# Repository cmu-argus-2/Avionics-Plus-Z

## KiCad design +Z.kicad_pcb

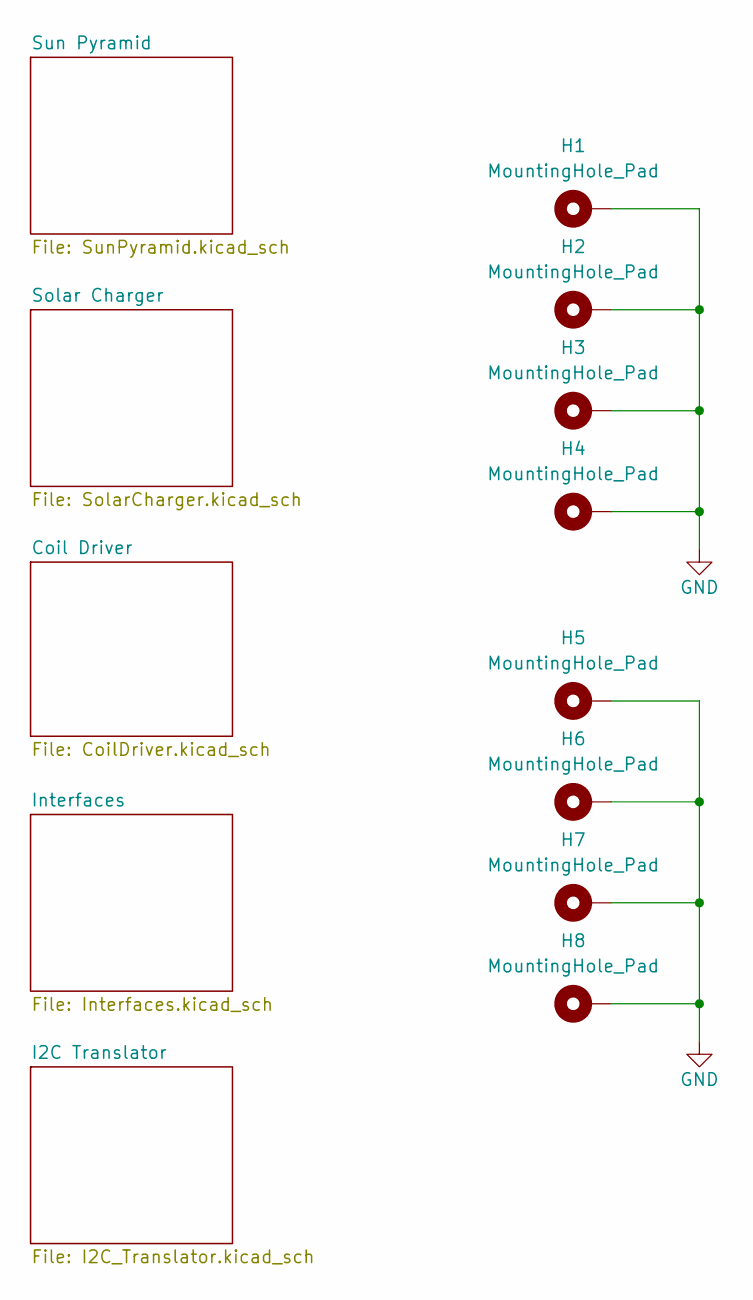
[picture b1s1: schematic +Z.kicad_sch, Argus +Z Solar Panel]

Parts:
H1, H2, H3, H4, H5, H6, H7, H8: MountingHole_Pad; MountingHole_3.2mm_M3_DIN965_Pad_TopBottom

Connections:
GND: H1.1, H2.1, H3.1, H4.1, H5.1, H6.1, H7.1, H8.1; also elsewhere on the board

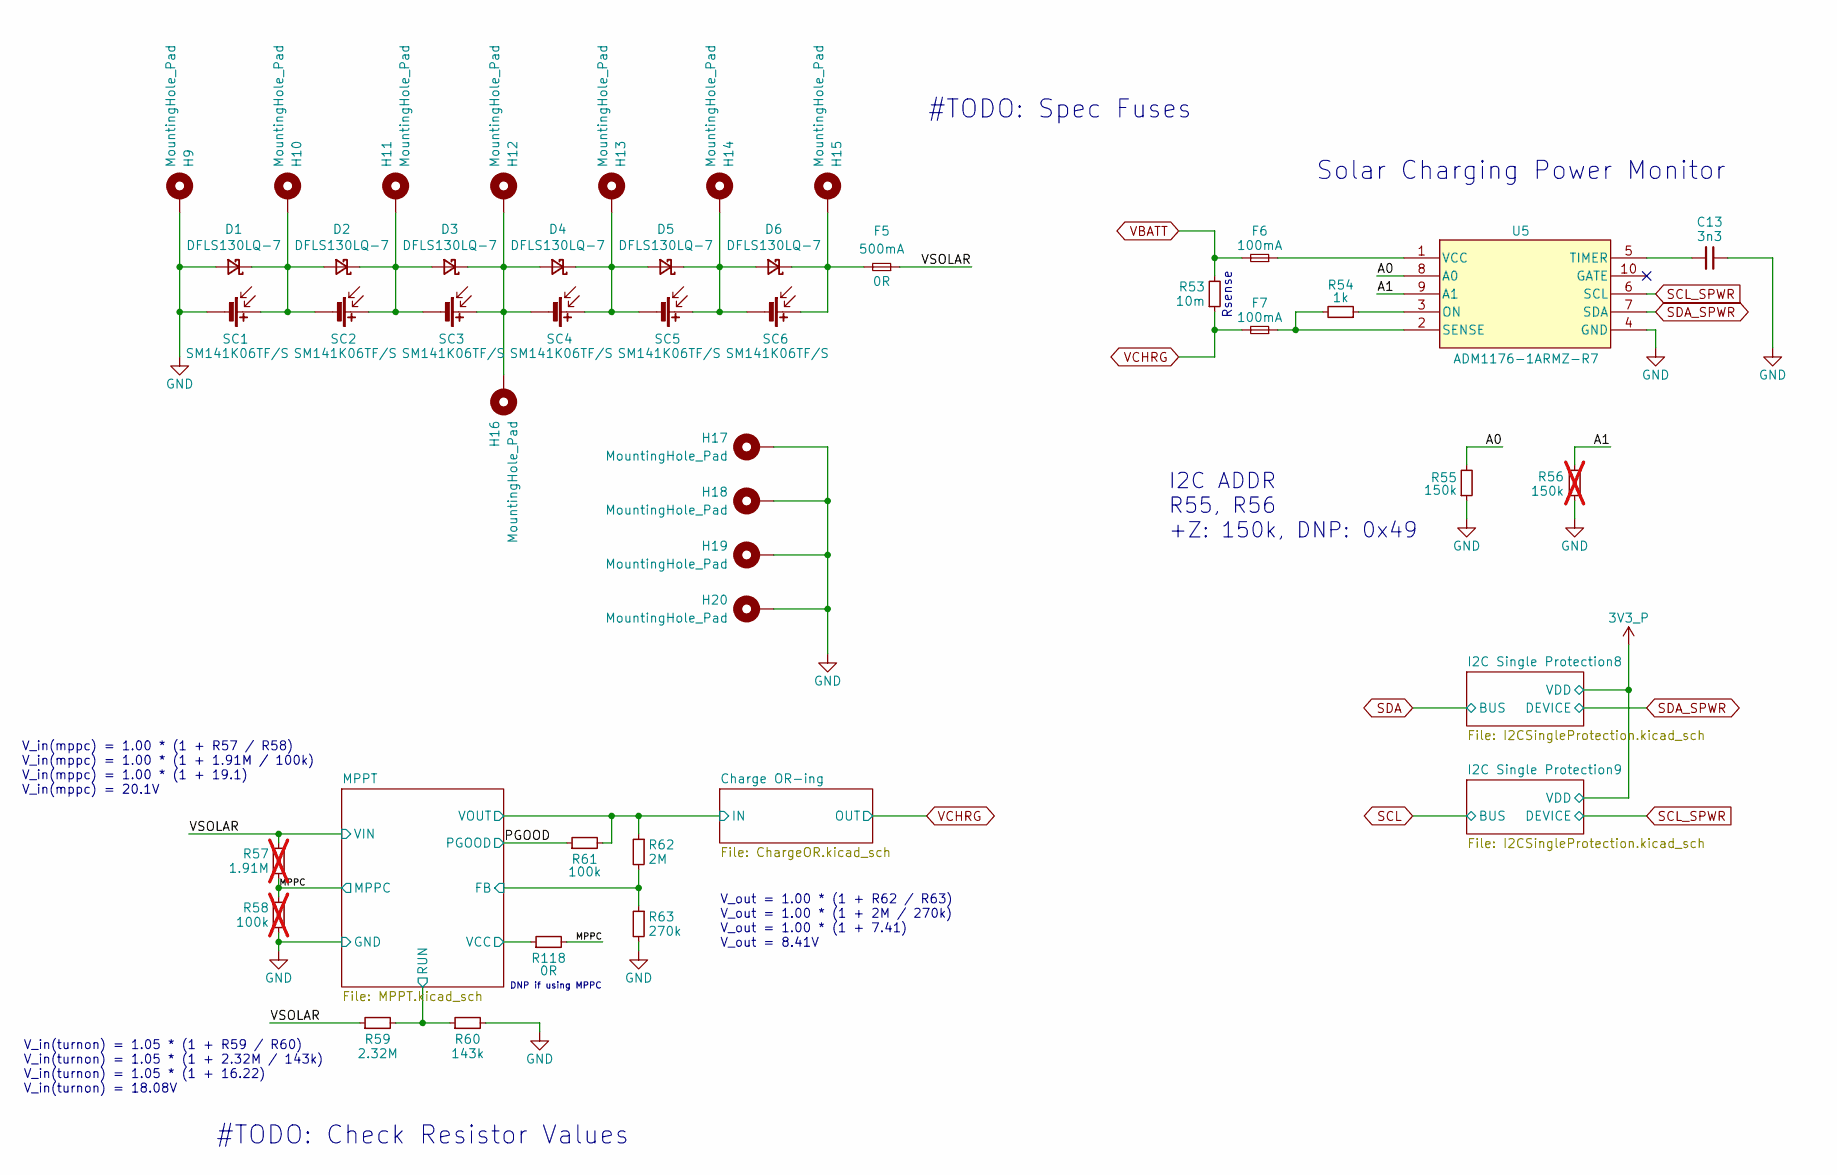
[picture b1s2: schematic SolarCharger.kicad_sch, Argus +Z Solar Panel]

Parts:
C13: 3n3; C_0603_1608Metric; MPN C3877267
D1, D2, D3, D4, D5, D6: DFLS130LQ-7; D_PowerDI-123
F5: 500mA; Fuse_0603_1608Metric
F6, F7: 100mA; Fuse_0603_1608Metric
H9, H10, H11, H12, H13, H14, H15, H16, H17, H18, H19, H20: MountingHole_Pad; TestPoint_Pad_D1.0mm
R53: 10m; R_2512_6332Metric; MPN C840621
R54: 1k; R_0603_1608Metric; MPN C2484712
R55: 150k; R_0603_1608Metric
R56: 150k; R_0603_1608Metric; MPN C402995; not fitted
R57: 1.91M; R_0603_1608Metric; not fitted
R58: 100k; R_0603_1608Metric; not fitted
R59: 2.32M; R_0603_1608Metric
R60: 143k; R_0603_1608Metric
R61: 100k; R_0603_1608Metric; MPN C237792
R62: 2M; R_0603_1608Metric
R63: 270k; R_0603_1608Metric; MPN C118142
R118: 0R; R_0603_1608Metric; MPN C237792
SC1, SC2, SC3, SC4, SC5, SC6: SM141K06TF/S; SM141K06TF_S
U5: ADM1176-1ARMZ-R7; MSOP-10_3x3mm_P0.5mm; Manufacturer_Part_Number ADM1176-1ARMZ-R7

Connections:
/Solar Charger/A0: R55.2, U5.8 (A0)
/Solar Charger/A1: R56.2, U5.9 (A1)
/Solar Charger/Charge OR-ing/IN: R61.2, R62.1; also elsewhere on the board
/Solar Charger/MPPC: R57.2, R58.1, R118.2; also elsewhere on the board
/Solar Charger/MPPT/FB: R62.2, R63.1; also elsewhere on the board
/Solar Charger/MPPT/RUN: R59.2, R60.1; also elsewhere on the board
/Solar Charger/MPPT/VCC: R118.1; also elsewhere on the board
/Solar Charger/PGOOD: R61.1; also elsewhere on the board
/Solar Charger/VSOLAR: F5.1, R57.1, R59.1; also elsewhere on the board
GND: C13.1, D1.2 (A), H9.1, H17.1, H18.1, H19.1, H20.1, R55.1, R56.1, R58.2, R60.2, R63.2, SC1.2 (-), U5.4 (GND); also elsewhere on the board
unnamed: D1.1 (K), D2.2 (A), H10.1, SC1.1 (+), SC2.2 (-)
unnamed: D2.1 (K), D3.2 (A), H11.1, SC2.1 (+), SC3.2 (-)
unnamed: D3.1 (K), D4.2 (A), H12.1, H16.1, SC3.1 (+), SC4.2 (-)
unnamed: D4.1 (K), D5.2 (A), H13.1, SC4.1 (+), SC5.2 (-)
unnamed: D5.1 (K), D6.2 (A), H14.1, SC5.1 (+), SC6.2 (-)
unnamed: D6.1 (K), F5.2, H15.1, SC6.1 (+)
unnamed: R54.1, U5.3 (ON)
unnamed: F7.1, R54.2, U5.2 (SENSE)
unnamed: C13.2, U5.5 (TIMER)
unnamed: F6.1, U5.1 (VCC)
SCL_SPWR: U5.6 (SCL); also elsewhere on the board
SDA_SPWR: U5.7 (SDA); also elsewhere on the board
VBATT: F6.2, R53.2; also elsewhere on the board
VCHRG: F7.2, R53.1; also elsewhere on the board

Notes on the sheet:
V_in(mppc) = 1.00 * (1 + R57 / R58) V_in(mppc) = 1.00 * (1 + 1.91M / 100k) V_in(mppc) = 1.00 * (1 + 19.1) V_in(mppc) = 20.1V
#TODO: Spec Fuses
V_in(turnon) = 1.05 * (1 + R59 / R60) V_in(turnon) = 1.05 * (1 + 2.32M / 143k) V_in(turnon) = 1.05 * (1 + 16.22) V_in(turnon) = 18.08V
Rsense
V_out = 1.00 * (1 + R62 / R63) V_out = 1.00 * (1 + 2M / 270k) V_out = 1.00 * (1 + 7.41) V_out = 8.41V
#TODO: Check Resistor Values
DNP if using MPPC
I2C ADDR R55, R56 +Z: 150k, DNP: 0x49
Solar Charging Power Monitor

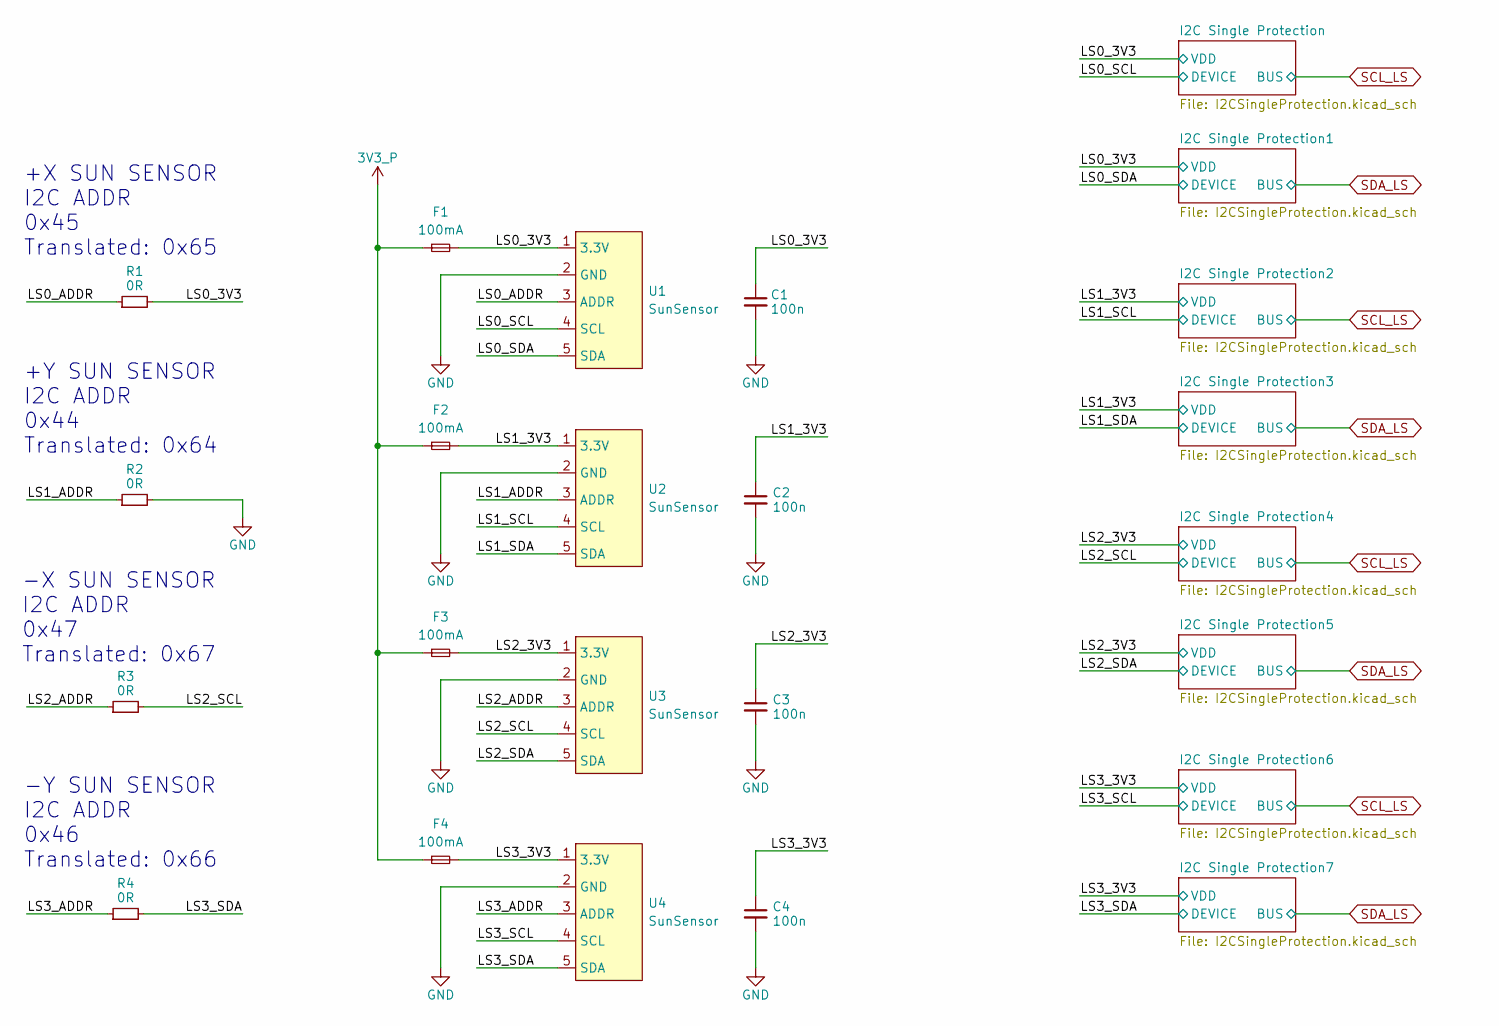
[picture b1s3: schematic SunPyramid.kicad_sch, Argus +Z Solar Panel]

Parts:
C1, C2, C3, C4: 100n; C_0603_1608Metric; MPN C307348
F1, F2, F3, F4: 100mA; Fuse_0603_1608Metric
R1, R2, R3, R4: 0R; R_0603_1608Metric; MPN C844915
U1, U2, U3, U4: SunSensor

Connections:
3V3_P: F1.1, F2.1, F3.1, F4.1; also elsewhere on the board
/Sun Pyramid/LS0_3V3: C1.1, F1.2, R1.2, U1.1 (3.3V); also elsewhere on the board
/Sun Pyramid/LS0_ADDR: R1.1, U1.3 (ADDR)
/Sun Pyramid/LS0_SCL: U1.4 (SCL); also elsewhere on the board
/Sun Pyramid/LS0_SDA: U1.5 (SDA); also elsewhere on the board
/Sun Pyramid/LS1_3V3: C2.1, F2.2, U2.1 (3.3V); also elsewhere on the board
/Sun Pyramid/LS1_ADDR: R2.1, U2.3 (ADDR)
/Sun Pyramid/LS1_SCL: U2.4 (SCL); also elsewhere on the board
/Sun Pyramid/LS1_SDA: U2.5 (SDA); also elsewhere on the board
/Sun Pyramid/LS2_3V3: C3.1, F3.2, U3.1 (3.3V); also elsewhere on the board
/Sun Pyramid/LS2_ADDR: R3.1, U3.3 (ADDR)
/Sun Pyramid/LS2_SCL: R3.2, U3.4 (SCL); also elsewhere on the board
/Sun Pyramid/LS2_SDA: U3.5 (SDA); also elsewhere on the board
/Sun Pyramid/LS3_3V3: C4.1, F4.2, U4.1 (3.3V); also elsewhere on the board
/Sun Pyramid/LS3_ADDR: R4.1, U4.3 (ADDR)
/Sun Pyramid/LS3_SCL: U4.4 (SCL); also elsewhere on the board
/Sun Pyramid/LS3_SDA: R4.2, U4.5 (SDA); also elsewhere on the board
GND: C1.2, C2.2, C3.2, C4.2, R2.2, U1.2 (GND), U2.2 (GND), U3.2 (GND), U4.2 (GND); also elsewhere on the board

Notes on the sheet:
-Y SUN SENSOR I2C ADDR 0x46 Translated: 0x66
-X SUN SENSOR I2C ADDR 0x47 Translated: 0x67
+X SUN SENSOR I2C ADDR 0x45 Translated: 0x65
+Y SUN SENSOR I2C ADDR 0x44 Translated: 0x64

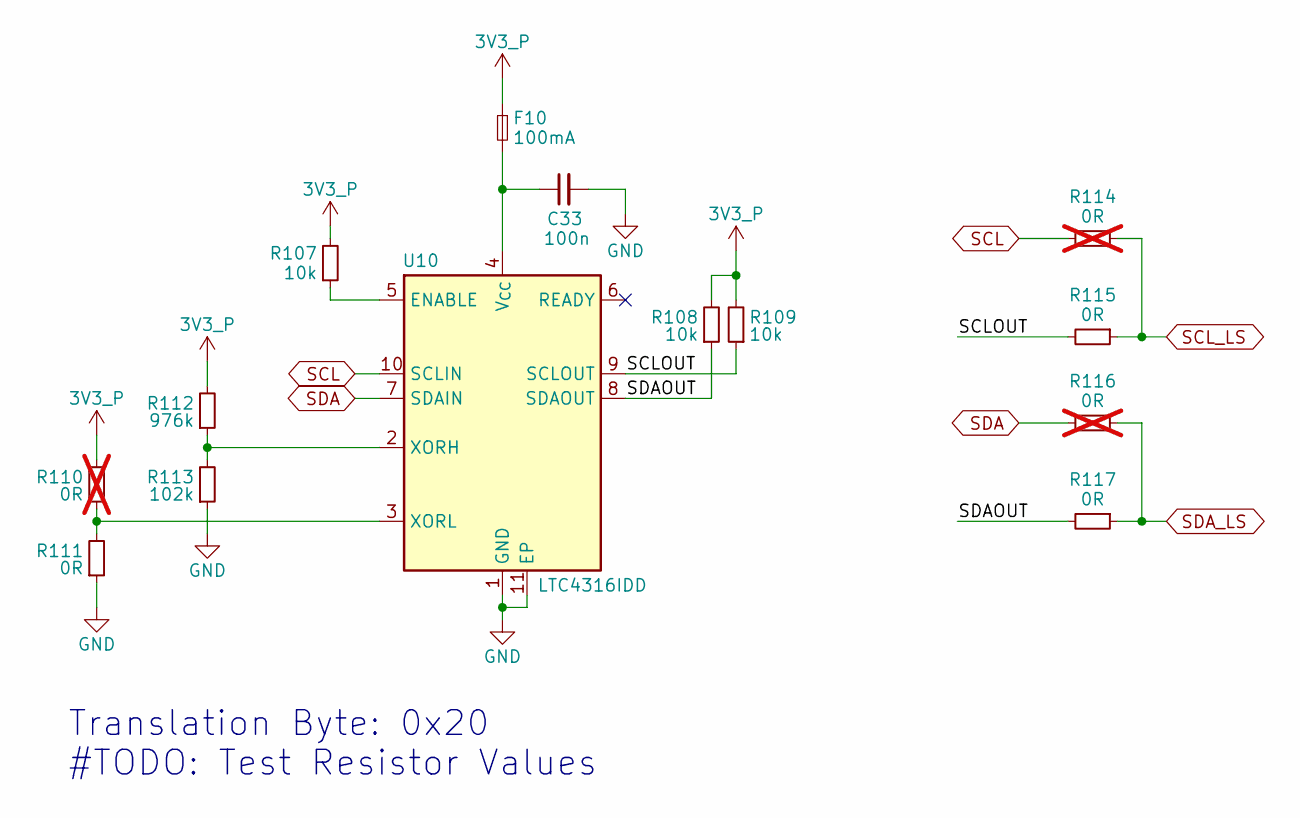
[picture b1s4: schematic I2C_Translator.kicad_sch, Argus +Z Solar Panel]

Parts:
C33: 100n; C_0603_1608Metric; MPN C307348
F10: 100mA; Fuse_0603_1608Metric
R107, R108, R109: 10k; R_0603_1608Metric; MPN C2479067
R110, R114, R116: 0R; R_0603_1608Metric; not fitted
R111, R115, R117: 0R; R_0603_1608Metric; MPN C844915
R112: 976k; R_0603_1608Metric
R113: 102k; R_0603_1608Metric
U10: LTC4316IDD; DFN-10-1EP_3x3mm_P0.5mm_EP1.65x2.38mm; MPN C688147

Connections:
3V3_P: F10.1, R107.2, R108.2, R109.2, R110.2, R112.2; also elsewhere on the board
/I2C Translator/SCLOUT: R109.1, R115.2, U10.9 (SCLOUT)
/I2C Translator/SDAOUT: R108.1, R117.2, U10.8 (SDAOUT)
GND: C33.2, R111.1, R113.1, U10.1 (GND), U10.11 (EP); also elsewhere on the board
unnamed: R107.1, U10.5 (ENABLE)
unnamed: C33.1, F10.2, U10.4 (V_{CC})
unnamed: R112.1, R113.2, U10.2 (XORH)
unnamed: R110.1, R111.2, U10.3 (XORL)
SCL: R114.2, U10.10 (SCLIN); also elsewhere on the board
SCL_LS: R114.1, R115.1; also elsewhere on the board
SDA: R116.2, U10.7 (SDAIN); also elsewhere on the board
SDA_LS: R116.1, R117.1; also elsewhere on the board

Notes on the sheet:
Translation Byte: 0x20 #TODO: Test Resistor Values

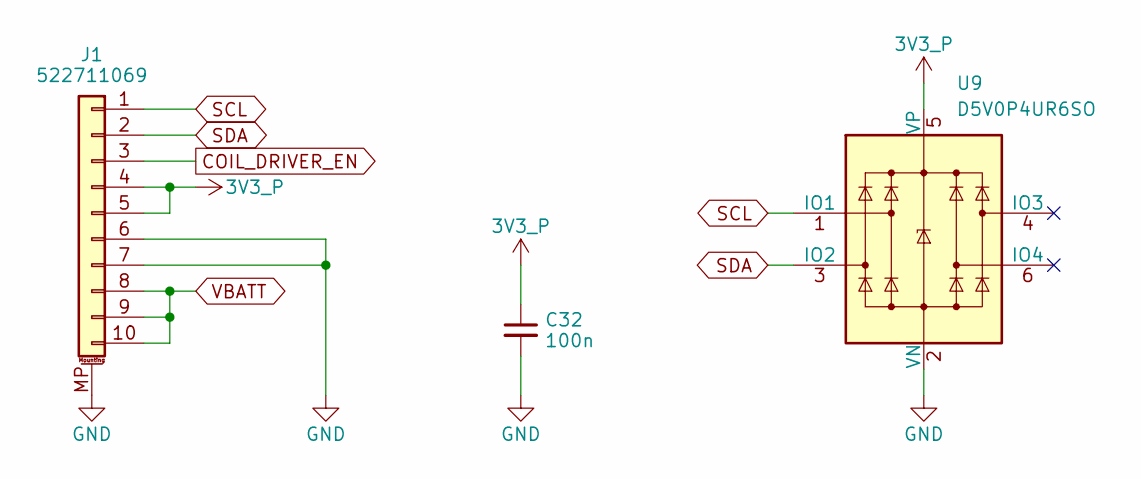
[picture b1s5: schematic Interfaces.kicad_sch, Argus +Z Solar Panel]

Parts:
C32: 100n; C_0603_1608Metric; MPN C307348
J1: 522711069; CON_522711069_MOL; MPN C588180
U9: D5V0P4UR6SO; SOT-23-6; MPN C531179

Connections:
3V3_P: C32.1, J1.4, J1.5, U9.5 (VP); also elsewhere on the board
COIL_DRIVER_EN: J1.3; also elsewhere on the board
GND: C32.2, J1.6, J1.7, J1.MP (MountPin), U9.2 (VN); also elsewhere on the board
SCL: J1.1, U9.1 (IO1); also elsewhere on the board
SDA: J1.2, U9.3 (IO2); also elsewhere on the board
VBATT: J1.8, J1.9, J1.10; also elsewhere on the board

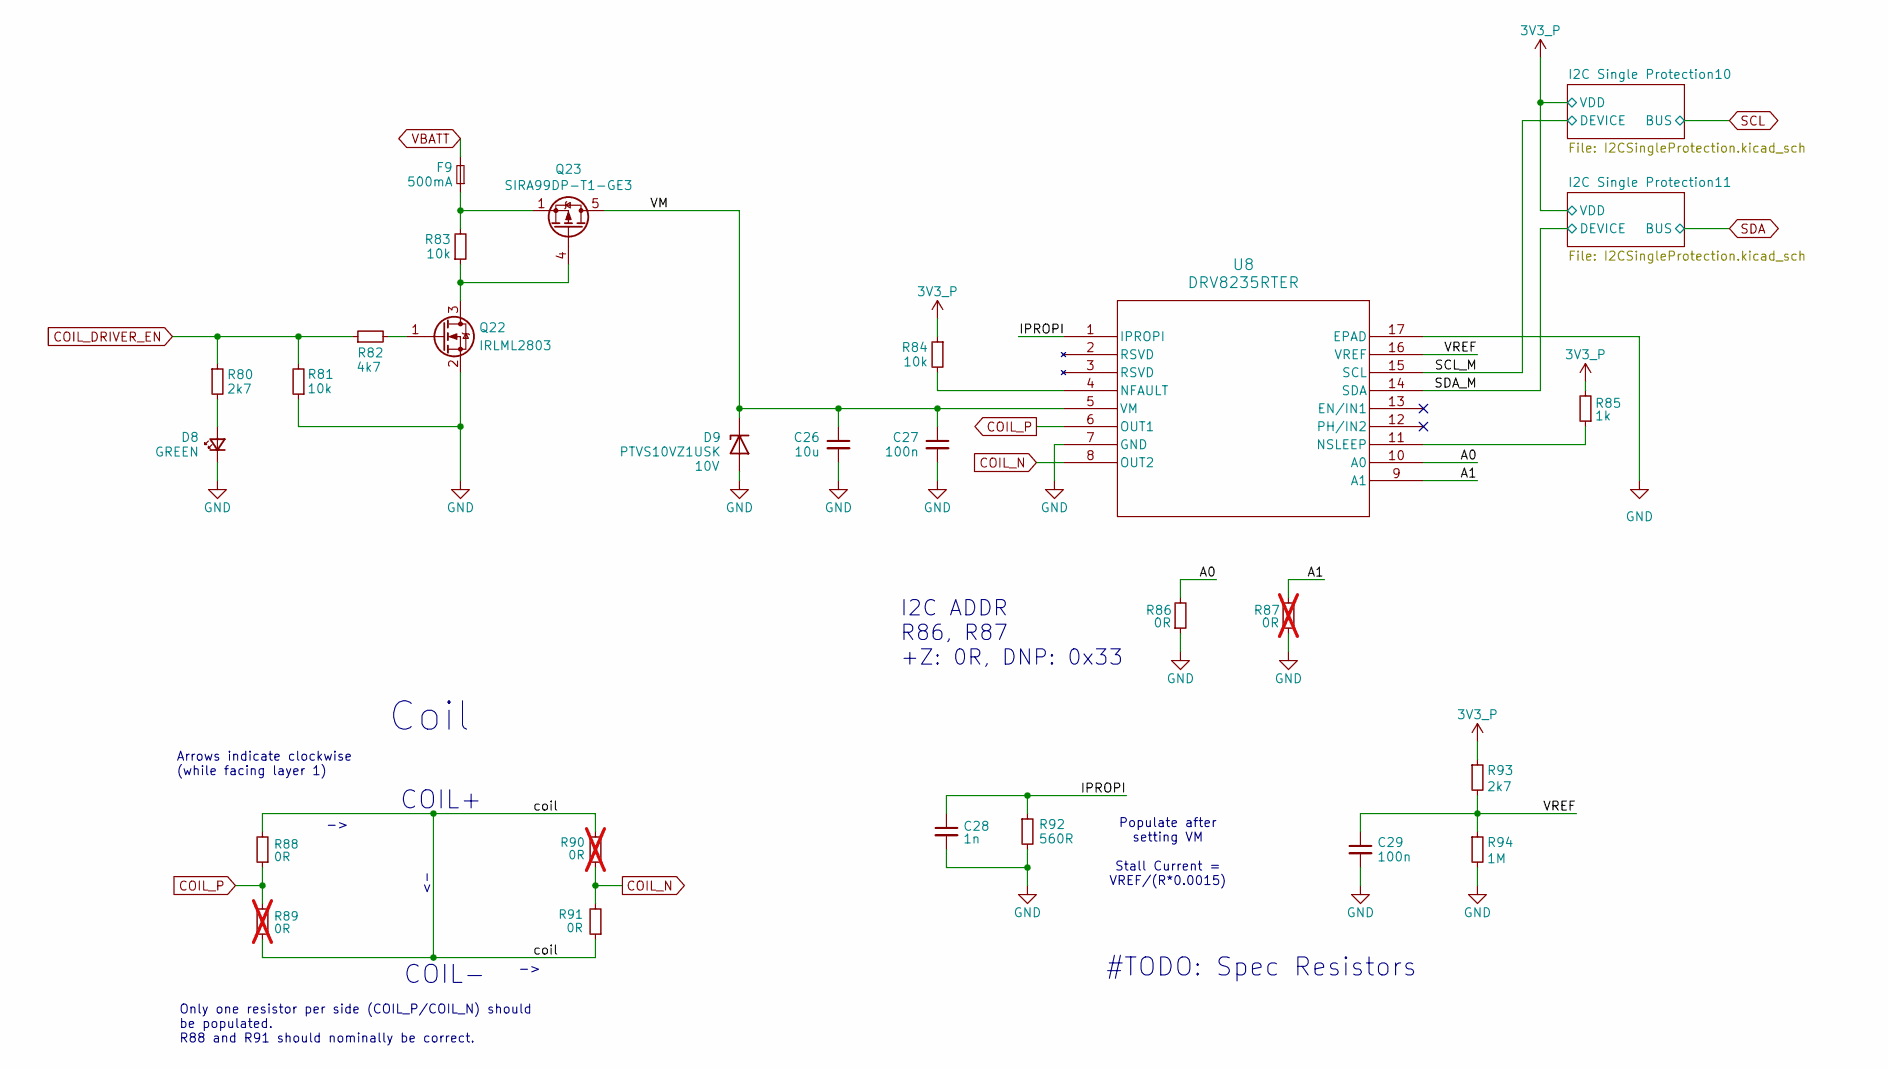
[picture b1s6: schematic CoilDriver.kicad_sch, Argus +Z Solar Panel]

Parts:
C26: 10u; C_1210_3225Metric; MPN C126617
C27, C29: 100n; C_0603_1608Metric; MPN C307348
C28: 1n; C_0603_1608Metric; MPN C161231
D8: GREEN; LED_0603_1608Metric; MPN C2909774
D9: PTVS10VZ1USK; Nexperia_DSN1608-2_1.6x0.8mm
F9: 500mA; Fuse_0603_1608Metric
Q22: IRLML2803; SOT-23; MPN C2590
Q23: SIRA99DP-T1-GE3; PowerPAK_SO-8_Single; MPN C3289459
R80: 2k7; R_0603_1608Metric; MPN C237112
R81, R83, R84: 10k; R_0603_1608Metric; MPN C2479067
R82: 4k7; R_0603_1608Metric; MPN C844931
R85: 1k; R_0603_1608Metric; MPN C2484712
R86, R88, R91: 0R; R_0603_1608Metric; MPN C844915
R87: 0R; R_0603_1608Metric; MPN C844915; not fitted
R89, R90: 0R; R_0603_1608Metric; not fitted
R92: 560R; R_0603_1608Metric
R93: 2k7; R_0603_1608Metric
R94: 1M; R_0603_1608Metric
U8: DRV8235RTER; WQFN16_RTE_TEX

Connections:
3V3_P: R84.1, R85.2, R93.1; also elsewhere on the board
/Coil Driver/A0: R86.2, U8.10 (A0)
/Coil Driver/A1: R87.2, U8.9 (A1)
/Coil Driver/IPROPI: C28.1, R92.1, U8.1 (IPROPI)
/Coil Driver/SCL_M: U8.15 (SCL); also elsewhere on the board
/Coil Driver/SDA_M: U8.14 (SDA); also elsewhere on the board
/Coil Driver/VM: C26.1, C27.1, D9.1 (K), Q23.5 (D), U8.5 (VM)
/Coil Driver/VREF: C29.1, R93.2, R94.1, U8.16 (VREF)
/Coil Driver/coil: R88.2, R89.1, R90.2, R91.1
COIL_DRIVER_EN: R80.1, R81.2, R82.1; also elsewhere on the board
COIL_N: R90.1, R91.2, U8.8 (OUT2)
COIL_P: R88.1, R89.2, U8.6 (OUT1)
GND: C26.2, C27.2, C28.2, C29.2, D8.1 (K), D9.2 (A), Q22.2 (S), R81.1, R86.1, R87.1, R92.2, R94.2, U8.7 (GND), U8.17 (EPAD); also elsewhere on the board
unnamed: D8.2 (A), R80.2
unnamed: F9.1, Q23.1 (S), Q23.2 (S), Q23.3 (S), R83.2
unnamed: Q22.3 (D), Q23.4 (G), R83.1
unnamed: Q22.1 (G), R82.2
unnamed: R84.2, U8.4 (NFAULT)
unnamed: R85.1, U8.11 (NSLEEP)
VBATT: F9.2; also elsewhere on the board

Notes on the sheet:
#TODO: Spec Resistors
I2C ADDR R86, R87 +Z: 0R, DNP: 0x33
COIL+
Coil
Arrows indicate clockwise (while facing layer 1)
Only one resistor per side (COIL_P/COIL_N) should be populated. R88 and R91 should nominally be correct.
COIL-
Populate after setting VM Stall Current = VREF/(R*0.0015)

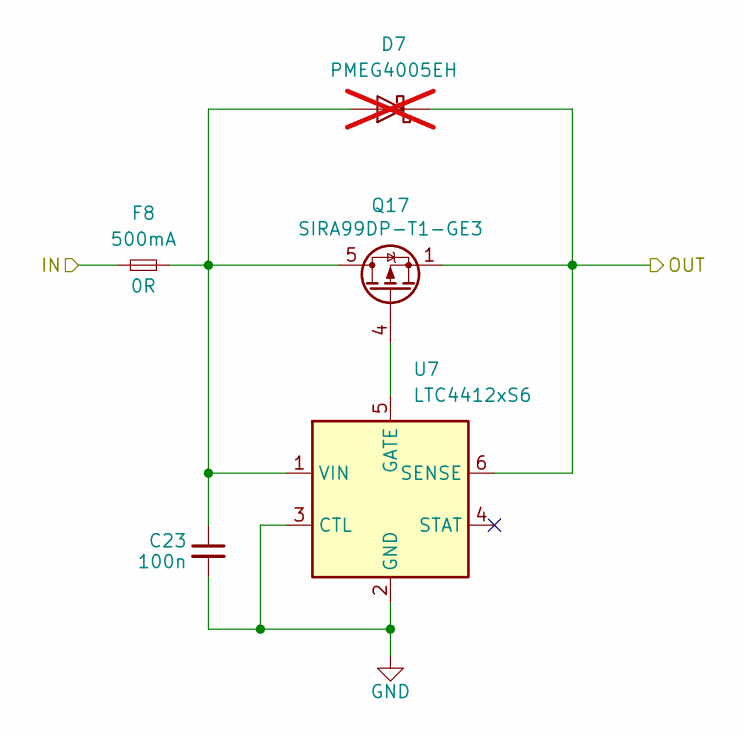
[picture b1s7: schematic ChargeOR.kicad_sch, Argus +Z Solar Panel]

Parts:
C23: 100n; C_0603_1608Metric; MPN C307348
D7: PMEG4005EH; D_SOD-123F; not fitted
F8: 500mA; Fuse_0603_1608Metric
Q17: SIRA99DP-T1-GE3; PowerPAK_SO-8_Single; MPN C3289459
U7: LTC4412xS6; TSOT-23-6

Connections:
/Solar Charger/Charge OR-ing/IN: F8.2; also elsewhere on the board
GND: C23.2, U7.2 (GND), U7.3 (CTL); also elsewhere on the board
unnamed: C23.1, D7.2 (A), F8.1, Q17.5 (D), U7.1 (VIN)
unnamed: Q17.4 (G), U7.5 (GATE)
VCHRG: D7.1 (K), Q17.1 (S), Q17.2 (S), Q17.3 (S), U7.6 (SENSE); also elsewhere on the board

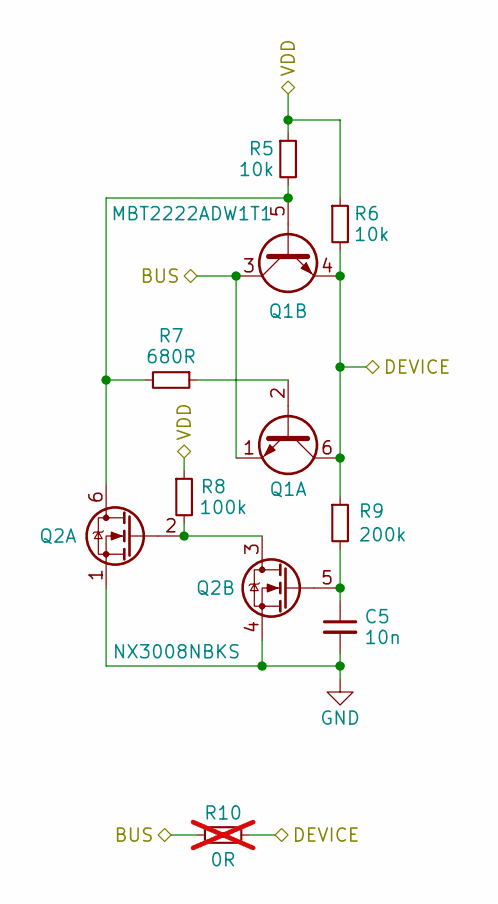
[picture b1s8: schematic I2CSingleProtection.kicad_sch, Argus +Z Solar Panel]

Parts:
C5: 10n; C_0603_1608Metric; MPN C161232
Q1: MBT2222ADW1T1; SOT-363_SC-70-6; Manufacturer_Part_Number MBT2222ADW1T1G
Q2: NX3008NBKS; SOT-363_SC-70-6; MPN C3280240
R5, R6: 10k; R_0603_1608Metric; MPN C2479067
R7: 680R; R_0603_1608Metric; MPN C844802
R8: 100k; R_0603_1608Metric; MPN C237792
R9: 200k; R_0603_1608Metric; MPN C118142
R10: 0R; R_0603_1608Metric; not fitted

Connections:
/Sun Pyramid/LS0_3V3: R5.1, R6.1, R8.1; also elsewhere on the board
/Sun Pyramid/LS0_SCL: Q1.4 (E2), Q1.6 (C1), R6.2, R9.1, R10.1; also elsewhere on the board
GND: C5.2, Q2.1 (S2), Q2.4 (S1); also elsewhere on the board
unnamed: Q1.2 (B1), R7.1
unnamed: Q1.5 (B2), Q2.6 (D1), R5.2, R7.2
unnamed: Q2.2 (G2), Q2.3 (D2), R8.2
unnamed: C5.1, Q2.5 (G1), R9.2
SCL_LS: Q1.1 (E1), Q1.3 (C2), R10.2; also elsewhere on the board

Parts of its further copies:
C6, C7, C8, C9, C10, C11, C12, C24, C25, C30, C31: 10n; C_0603_1608Metric; MPN C161232
Q3, Q5, Q7, Q9, Q11, Q13, Q15, Q18, Q20, Q24, Q26: MBT2222ADW1T1; SOT-363_SC-70-6; Manufacturer_Part_Number MBT2222ADW1T1G
Q4, Q6, Q8, Q10, Q12, Q14, Q16, Q19, Q21, Q25, Q27: NX3008NBKS; SOT-363_SC-70-6; MPN C3280240
R11, R12, R17, R18, R23, R24, R29, R30, R35, R36, R41, R42, R47, R48, R68, R69, R74, R75, R95, R96, R101, R102: 10k; R_0603_1608Metric; MPN C2479067
R13, R19, R25, R31, R37, R43, R49, R70, R76, R97, R103: 680R; R_0603_1608Metric; MPN C844802
R14, R20, R26, R32, R38, R44, R50, R71, R77, R98, R104: 100k; R_0603_1608Metric; MPN C237792
R15, R21, R27, R33, R39, R45, R51, R72, R78, R99, R105: 200k; R_0603_1608Metric; MPN C118142
R16, R22, R28, R34, R40, R46, R52, R73, R79, R100, R106: 0R; R_0603_1608Metric; not fitted

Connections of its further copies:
3V3_P: R68.1, R69.1, R71.1, R74.1, R75.1, R77.1, R95.1, R96.1, R98.1, R101.1, R102.1, R104.1; also elsewhere on the board
/Coil Driver/SCL_M: Q24.4 (E2), Q24.6 (C1), R96.2, R99.1, R100.1; also elsewhere on the board
/Coil Driver/SDA_M: Q26.4 (E2), Q26.6 (C1), R102.2, R105.1, R106.1; also elsewhere on the board
/Sun Pyramid/LS0_3V3: R11.1, R12.1, R14.1; also elsewhere on the board
/Sun Pyramid/LS0_SDA: Q3.4 (E2), Q3.6 (C1), R12.2, R15.1, R16.1; also elsewhere on the board
/Sun Pyramid/LS1_3V3: R17.1, R18.1, R20.1, R23.1, R24.1, R26.1; also elsewhere on the board
/Sun Pyramid/LS1_SCL: Q5.4 (E2), Q5.6 (C1), R18.2, R21.1, R22.1; also elsewhere on the board
/Sun Pyramid/LS1_SDA: Q7.4 (E2), Q7.6 (C1), R24.2, R27.1, R28.1; also elsewhere on the board
/Sun Pyramid/LS2_3V3: R29.1, R30.1, R32.1, R35.1, R36.1, R38.1; also elsewhere on the board
/Sun Pyramid/LS2_SCL: Q9.4 (E2), Q9.6 (C1), R30.2, R33.1, R34.1; also elsewhere on the board
/Sun Pyramid/LS2_SDA: Q11.4 (E2), Q11.6 (C1), R36.2, R39.1, R40.1; also elsewhere on the board
/Sun Pyramid/LS3_3V3: R41.1, R42.1, R44.1, R47.1, R48.1, R50.1; also elsewhere on the board
/Sun Pyramid/LS3_SCL: Q13.4 (E2), Q13.6 (C1), R42.2, R45.1, R46.1; also elsewhere on the board
/Sun Pyramid/LS3_SDA: Q15.4 (E2), Q15.6 (C1), R48.2, R51.1, R52.1; also elsewhere on the board
GND: C6.2, C7.2, C8.2, C9.2, C10.2, C11.2, C12.2, C24.2, C25.2, C30.2, C31.2, Q4.1 (S2), Q4.4 (S1), Q6.1 (S2), Q6.4 (S1), Q8.1 (S2), Q8.4 (S1), Q10.1 (S2), Q10.4 (S1), Q12.1 (S2), Q12.4 (S1), Q14.1 (S2), Q14.4 (S1), Q16.1 (S2), Q16.4 (S1), Q19.1 (S2), Q19.4 (S1), Q21.1 (S2), Q21.4 (S1), Q25.1 (S2), Q25.4 (S1), Q27.1 (S2), Q27.4 (S1); also elsewhere on the board
unnamed: Q3.2 (B1), R13.1
unnamed: Q3.5 (B2), Q4.6 (D1), R11.2, R13.2
unnamed: Q4.2 (G2), Q4.3 (D2), R14.2
unnamed: C6.1, Q4.5 (G1), R15.2
unnamed: Q5.2 (B1), R19.1
unnamed: Q5.5 (B2), Q6.6 (D1), R17.2, R19.2
unnamed: Q6.2 (G2), Q6.3 (D2), R20.2
unnamed: C7.1, Q6.5 (G1), R21.2
unnamed: Q7.2 (B1), R25.1
unnamed: Q7.5 (B2), Q8.6 (D1), R23.2, R25.2
unnamed: Q8.2 (G2), Q8.3 (D2), R26.2
unnamed: C8.1, Q8.5 (G1), R27.2
unnamed: Q9.2 (B1), R31.1
unnamed: Q9.5 (B2), Q10.6 (D1), R29.2, R31.2
unnamed: Q10.2 (G2), Q10.3 (D2), R32.2
unnamed: C9.1, Q10.5 (G1), R33.2
unnamed: Q11.2 (B1), R37.1
unnamed: Q11.5 (B2), Q12.6 (D1), R35.2, R37.2
unnamed: Q12.2 (G2), Q12.3 (D2), R38.2
unnamed: C10.1, Q12.5 (G1), R39.2
unnamed: Q13.2 (B1), R43.1
unnamed: Q13.5 (B2), Q14.6 (D1), R41.2, R43.2
unnamed: Q14.2 (G2), Q14.3 (D2), R44.2
unnamed: C11.1, Q14.5 (G1), R45.2
unnamed: Q15.2 (B1), R49.1
unnamed: Q15.5 (B2), Q16.6 (D1), R47.2, R49.2
unnamed: Q16.2 (G2), Q16.3 (D2), R50.2
unnamed: C12.1, Q16.5 (G1), R51.2
unnamed: Q18.2 (B1), R70.1
unnamed: Q18.5 (B2), Q19.6 (D1), R68.2, R70.2
unnamed: Q19.2 (G2), Q19.3 (D2), R71.2
unnamed: C24.1, Q19.5 (G1), R72.2
unnamed: Q20.2 (B1), R76.1
unnamed: Q20.5 (B2), Q21.6 (D1), R74.2, R76.2
unnamed: Q21.2 (G2), Q21.3 (D2), R77.2
unnamed: C25.1, Q21.5 (G1), R78.2
unnamed: Q24.2 (B1), R97.1
unnamed: Q24.5 (B2), Q25.6 (D1), R95.2, R97.2
unnamed: Q25.2 (G2), Q25.3 (D2), R98.2
unnamed: C30.1, Q25.5 (G1), R99.2
unnamed: Q26.2 (B1), R103.1
unnamed: Q26.5 (B2), Q27.6 (D1), R101.2, R103.2
unnamed: Q27.2 (G2), Q27.3 (D2), R104.2
unnamed: C31.1, Q27.5 (G1), R105.2
SCL: Q20.1 (E1), Q20.3 (C2), Q24.1 (E1), Q24.3 (C2), R79.2, R100.2; also elsewhere on the board
SCL_LS: Q5.1 (E1), Q5.3 (C2), Q9.1 (E1), Q9.3 (C2), Q13.1 (E1), Q13.3 (C2), R22.2, R34.2, R46.2; also elsewhere on the board
SCL_SPWR: Q20.4 (E2), Q20.6 (C1), R75.2, R78.1, R79.1; also elsewhere on the board
SDA: Q18.1 (E1), Q18.3 (C2), Q26.1 (E1), Q26.3 (C2), R73.2, R106.2; also elsewhere on the board
SDA_LS: Q3.1 (E1), Q3.3 (C2), Q7.1 (E1), Q7.3 (C2), Q11.1 (E1), Q11.3 (C2), Q15.1 (E1), Q15.3 (C2), R16.2, R28.2, R40.2, R52.2; also elsewhere on the board
SDA_SPWR: Q18.4 (E2), Q18.6 (C1), R69.2, R72.1, R73.1; also elsewhere on the board

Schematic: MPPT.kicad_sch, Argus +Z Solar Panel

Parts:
C14, C21: 47u; C_1210_3225Metric; Voltage 16V; Mfr. # GRM32EC81C476KE15L
C15: 10u; C_1210_3225Metric; MPN C126617
C16, C17, C20: 1u; C_0805_2012Metric; MPN C2214844
C18, C19: 22n; C_0603_1608Metric; MPN C161234
C22: 4u7; C_0603_1608Metric; MPN C437575
L1: 6.8u; L_Coilcraft_LPS4018; Mfr. # LPS4018-472
R64: 0R; R_0603_1608Metric; not fitted
R65, R66, R67: 0R; R_0603_1608Metric; MPN C844915
U6: LTC3130IUDC; QFN-20-1EP_3x4mm_P0.5mm_EP1.65x2.65mm; MPN C684244

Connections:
/Solar Charger/Charge OR-ing/IN: C20.1, C21.1, U6.14 (VOUT); also elsewhere on the board
/Solar Charger/MPPC: U6.6 (MPPC); also elsewhere on the board
/Solar Charger/MPPT/FB: U6.9 (FB); also elsewhere on the board
/Solar Charger/MPPT/RUN: U6.4 (RUN); also elsewhere on the board
/Solar Charger/MPPT/VCC: C22.1, R64.2, U6.5 (VCC); also elsewhere on the board
/Solar Charger/PGOOD: U6.13 (PGOOD); also elsewhere on the board
/Solar Charger/VSOLAR: C14.1, C15.1, C16.1, C17.1, U6.2 (PVIN), U6.3 (VIN); also elsewhere on the board
GND: C14.2, C15.2, C16.2, C17.2, C20.2, C21.2, C22.2, R65.2, R66.2, R67.1, U6.7 (GND), U6.8 (GND), U6.17 (GND), U6.18 (PGND), U6.19 (PGND), U6.21 (GND); also elsewhere on the board
unnamed: C18.2, U6.1 (BST1)
unnamed: C19.1, U6.16 (BST2)
unnamed: R67.2, U6.12 (EXTVCC)
unnamed: R64.1, R65.1, U6.10 (ILIM)
unnamed: R66.1, U6.11 (MODE)
unnamed: C18.1, L1.1, U6.20 (SW1)
unnamed: C19.2, L1.2, U6.15 (SW2)

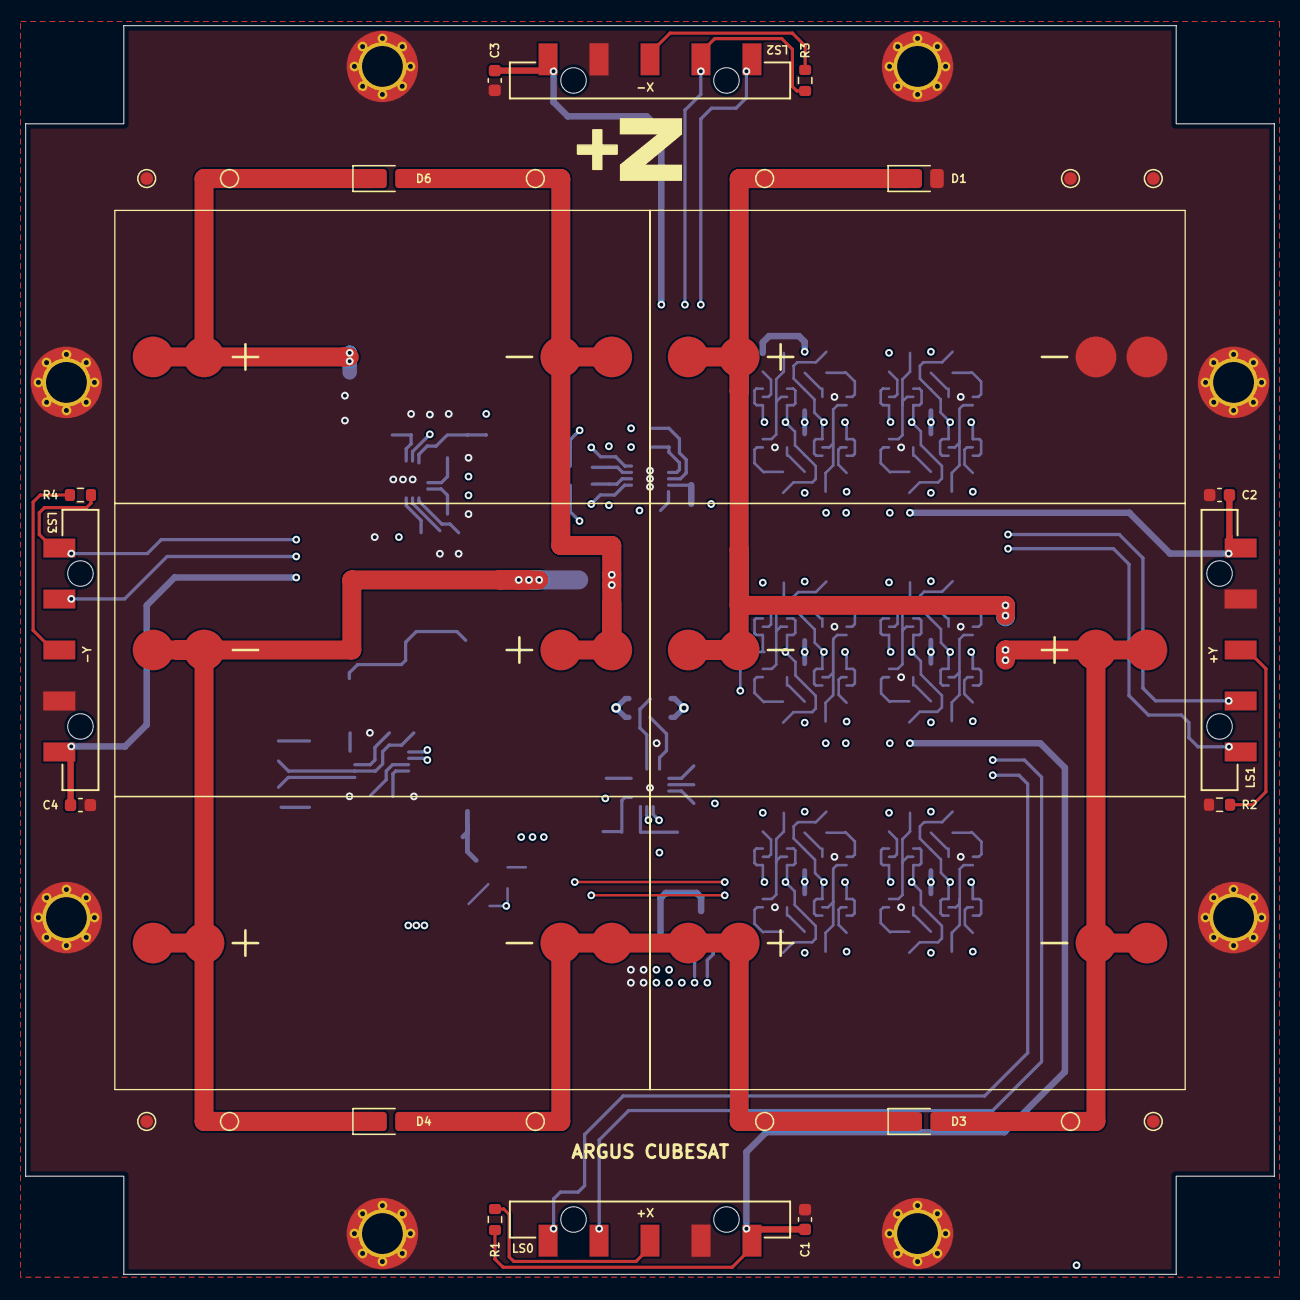
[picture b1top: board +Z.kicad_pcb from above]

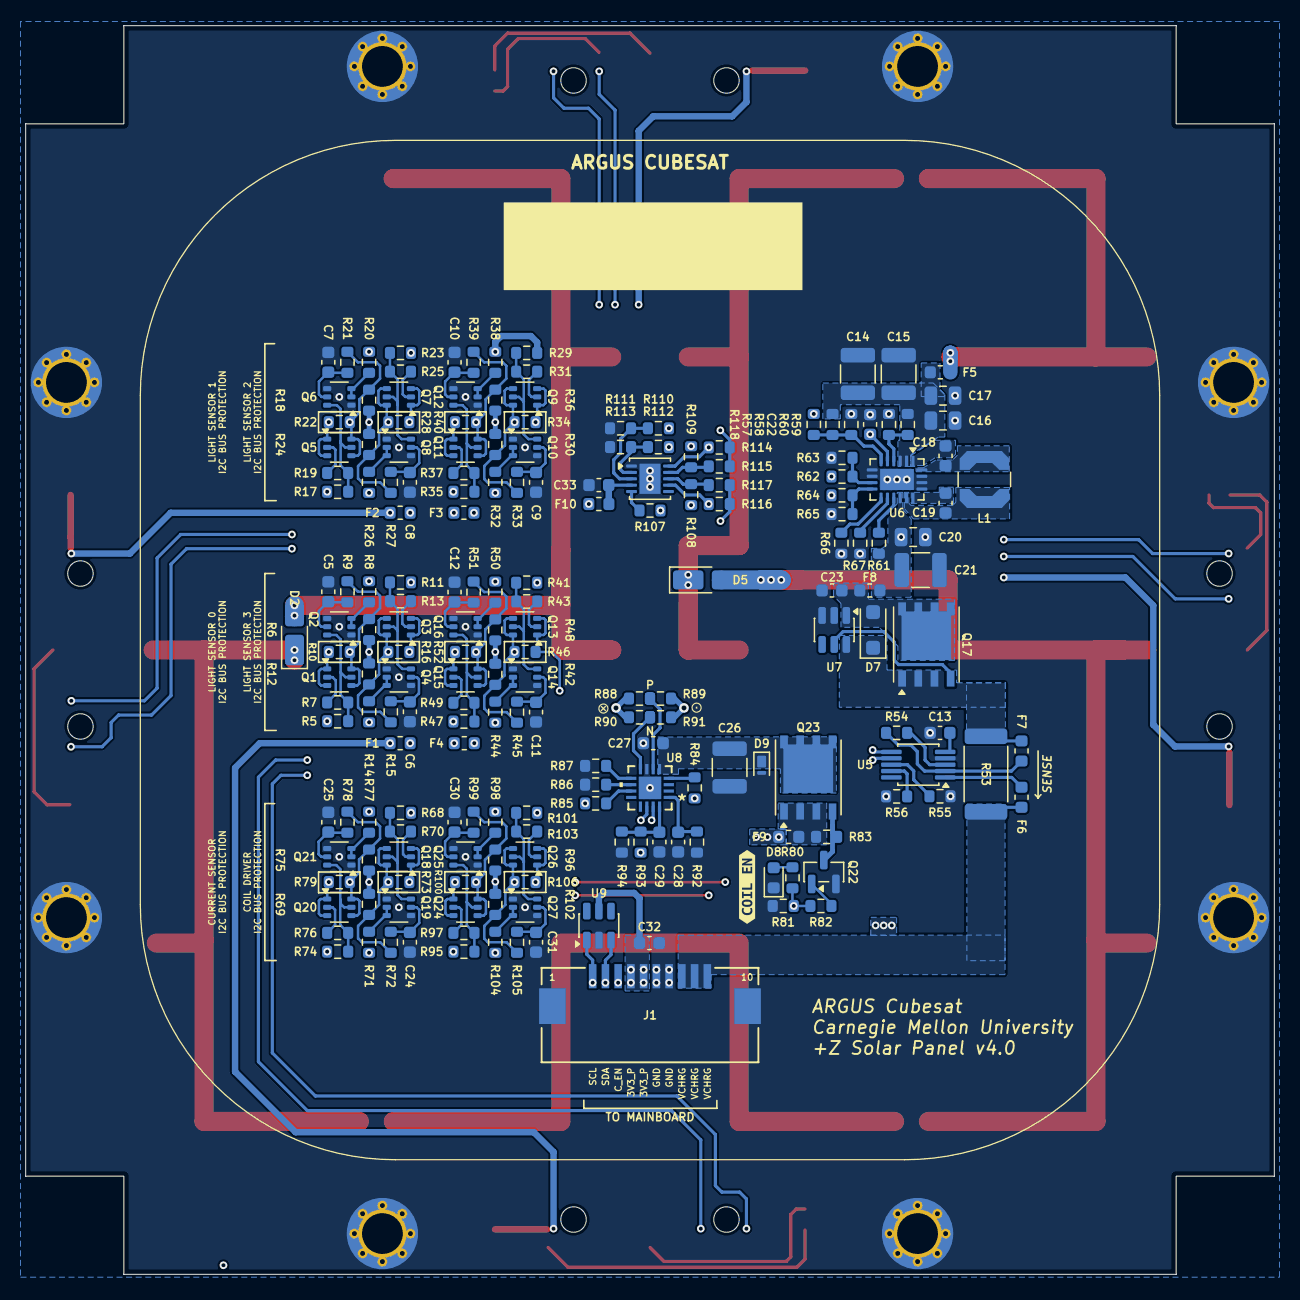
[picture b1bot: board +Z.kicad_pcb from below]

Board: 4 copper layers, 98.0 x 98.0 mm, 237 parts (194 on the bottom side), 125 nets.

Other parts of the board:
Ref**: Val**; ypanel
kibuzzard-680A9610: G***; kibuzzard-680A9610
